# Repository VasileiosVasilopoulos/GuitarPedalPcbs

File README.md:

## Guitar Pedal Pcb Projects

Collection of Guitar and Bass Pedal pcbs 
designed with the free version of [Eagle](https://www.autodesk.com/products/eagle/free-download?plc=F360&term=1-YEAR&support=ADVANCED&quantity=1).

### Licence

The designs are free to use non-commercially.

I would not recommend using commercially since 
copyrights may apply to the schematics / fonts etc.

### List of effects

#### Fuzz 
- [Randy's Gut](Randys_Gut) (EQD Dirt Transmitter clone)
- [Zeus](Zeus) (Similar to EQD Blach Ash)

#### Octaver
- [Poseidon](Poseidon) (EQD Tentacle clone)

#### Digital
- [Deep Space](DeepSpace) (Add-on shield for teensy with Audioshield)

#### Other
- [3PDT](3PDT_Breakout) Foot Switch Breakout Board

### Resources 

I'd like to thank all the people offering to the DIY community and link some resources that helped me get familiar with designing pcb's.

Jeremy Blum's [youtube channel](https://www.youtube.com/user/sciguy14) has some good tutorials for EAGLE basics.

Effect's Layout [blog](http://effectslayouts.blogspot.com/) / [youtube](https://www.youtube.com/channel/UCuCJhqsyaGveg0PjLbAGcdQ) has a big variety of pedal designs for perfboards / pcb etching. Also a nice tutorial series for EAGLE and a pack of EAGLE libraries with focus to pcb design for pedals. 

[MadBeanPedals](https://www.madbeanpedals.com/) has some designs and tutorials for homemade pcb etching. He also has a very helpful EAGLE library.

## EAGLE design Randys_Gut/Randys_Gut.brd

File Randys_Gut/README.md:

## Randy's Gut

Fuzz

#### Status:
```diff
+ Verified
```

Schematic based on EQD Dirt Transmitter

### Board Preview: 

Front             |  Back
:-------------------------:|:-------------------------:
  |  
  |  

### Drill Template 

[Drill Template](Photos/Randys_Gut_Drill.pdf)

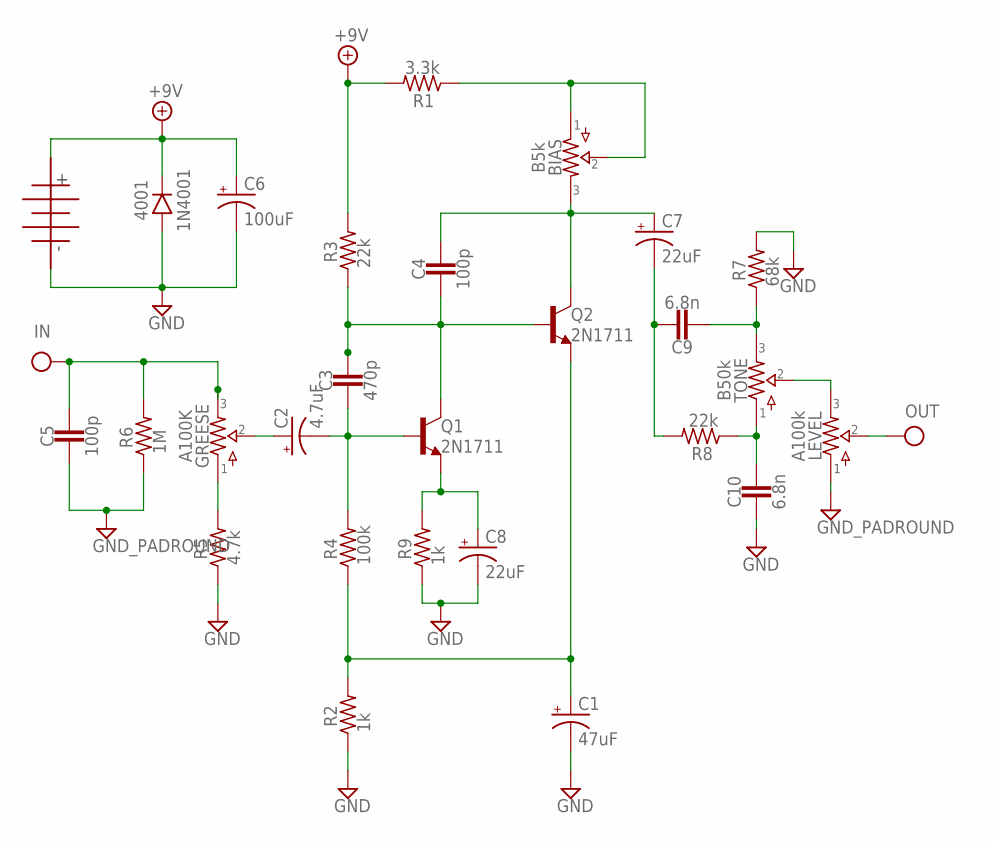
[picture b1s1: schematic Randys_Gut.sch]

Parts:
4001: 1N4001; DO41-3
BIAS: B5k; 16MM_B.MOUNT
C1: 47uF; 063_025
C2: 4.7uF; 050_020_1
C3: 470p; 0.2".SML
C4, C5: 100p; 0.2".SML
C6: 100uF; 063_025
C7, C8: 22uF; 050_020_1
C9, C10: 6.8n; 0.2".SML
GI: GND_PADROUND; ROUND
GO: GND_PADROUND; ROUND
GREESE: A100K; 16MM_B.MOUNT
IN: IN; SQUARE
LEVEL: A100k; 16MM_B.MOUNT
OUT: OUT; SQUARE
PWR: BATTERYBAT2; BATTERY2
Q1, Q2: 2N1711; TO18
R1: 3.3k; R0207/3
R2, R9: 1k; R0207/3
R3, R8: 22k; R0207/3
R4: 100k; R0207/3
R5: 4.7k; R0207/3
R6: 1M; R0207/3
R7: 68k; R0207/3
TONE: B50k; 16MM_B.MOUNT

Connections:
+9V: 4001.C, C6.+, PWR.P$1, R1.2, R3.2
C3: C2.-, C3.2, Q1.2 (B), R4.2
GND: 4001.A, C1.-, C5.2, C6.-, C8.-, C10.2, GI.1, GO.1, LEVEL.1, PWR.P$2, R2.1, R5.1, R6.1, R7.2, R9.1
IN: C5.1, GREESE.3, IN.1, R6.2
unnamed: GREESE.1, R5.2
unnamed: C2.+, GREESE.2
unnamed: C1.+, Q2.1 (E), R2.2, R4.1
unnamed: C3.1, C4.2, Q1.3 (C), Q2.2 (B), R3.1
unnamed: C8.+, Q1.1 (E), R9.2
unnamed: BIAS.3, C4.1, C7.+, Q2.3 (C)
unnamed: C7.-, C9.1, R8.2
unnamed: BIAS.1, BIAS.2, R1.1
unnamed: C9.2, R7.1, TONE.3
unnamed: C10.1, R8.1, TONE.1
unnamed: LEVEL.3, TONE.2
OUT: LEVEL.2, OUT.1

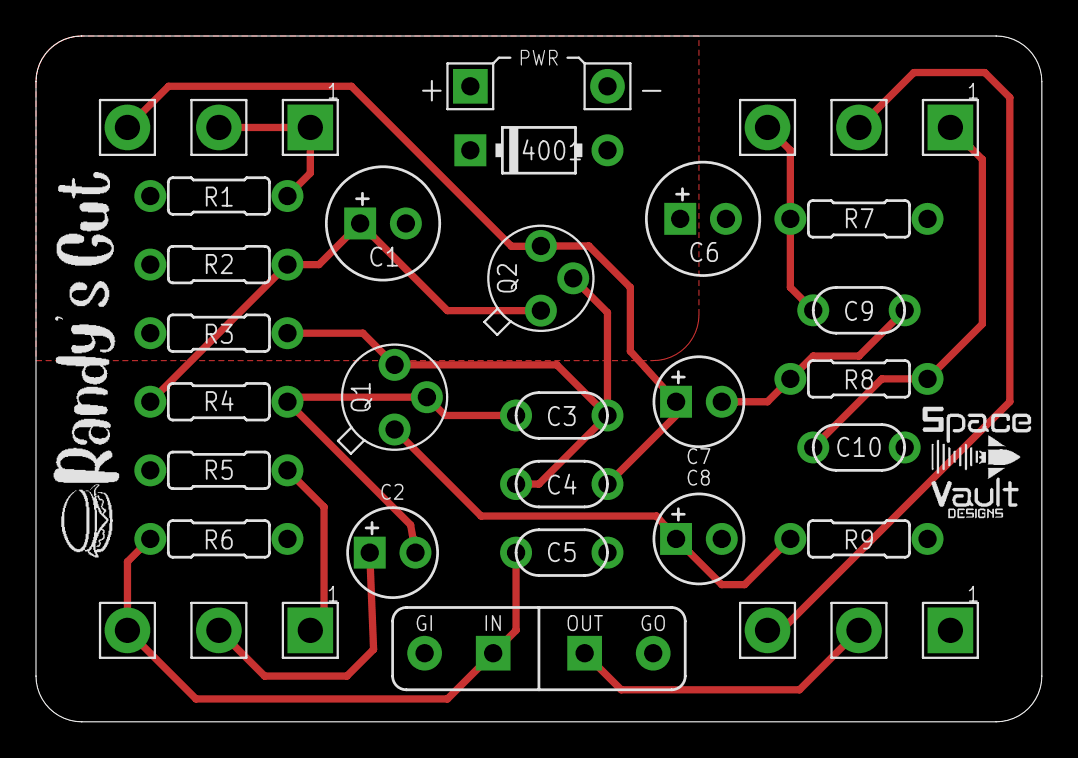
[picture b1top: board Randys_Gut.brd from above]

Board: 2 copper layers, 55.9 x 38.1 mm, 31 parts (0 on the bottom side), 16 nets.

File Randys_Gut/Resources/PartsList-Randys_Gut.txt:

_______________________________
R

1k   2
3.3k
4.7k
22k  2
68k
100k
1m
_______________________________
C 

100p  2 
470p
6.8n 2

4.7uF
22uF  2
47uF
100uF

_______________________________
D

1N4001

_______________________________
IC
2N1711 2

_______________________________
POTS

5kB
50kB
100kA 2

_______________________________
Other

2 Mono Jacks Enclosed
LED
Power Supply Socket
Pot Dusters
Pot Knobs

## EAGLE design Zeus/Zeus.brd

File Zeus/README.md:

## Zeus

Fuzz

#### Status:
```diff
+ Verified
```

Schematic similar to the EQD Dirt Transmitter.

### Board Preview: 

Front             |  Back
:-------------------------:|:-------------------------:
  |  
  |  

### Drill Template 

[Drill Template](Photos/ZeusDrill.pdf)

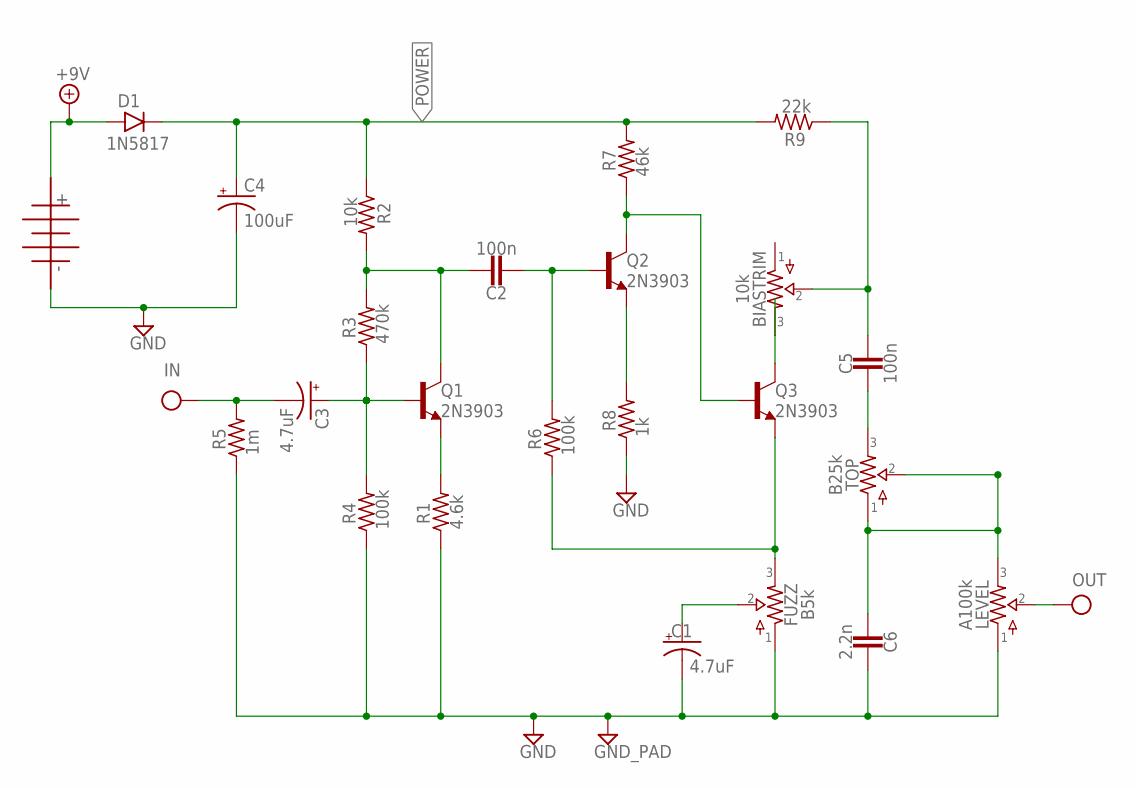
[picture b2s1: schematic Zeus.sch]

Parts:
9V: BATTERYBAT2; BATTERY2
BIASTRIM: 10k; TRIM1
C1, C3: 4.7uF; 050_020_1
C2, C5: 100n; 0.2".SML
C4: 100uF; 063_025
C6: 2.2n; 0.2".SML
D1: 1N5817; DO41-3
FUZZ: B5k; 16MM_B.MOUNT
GND: GND_PAD; SQUARE
IN: IN; SQUARE
LEVEL: A100k; 16MM_B.MOUNT
OUT: OUT; SQUARE
Q1, Q2, Q3: 2N3903; TO92
R1: 4.6k; R0207/3
R2: 10k; R0207/3
R3: 470k; R0207/3
R4, R6: 100k; R0207/3
R5: 1m; R0207/3
R7: 46k; R0207/3
R8: 1k; R0207/3
R9: 22k; R0207/3
TOP: B25k; 16MM_B.MOUNT

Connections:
+9V: 9V.P$1, D1.A
GND: 9V.P$2, C1.-, C4.-, C6.1, FUZZ.1, GND.1, LEVEL.1, R1.1, R4.1, R5.1, R8.1
IN: C3.-, IN.1, R5.2
unnamed: C2.1, Q1.1 (C), R2.2, R3.2
unnamed: C2.2, Q2.2 (B), R6.2
unnamed: C3.+, Q1.2 (B), R3.1, R4.2
unnamed: C5.2, TOP.3
unnamed: Q1.3 (E), R1.2
unnamed: Q2.3 (E), R8.2
unnamed: FUZZ.3, Q3.3 (E), R6.1
unnamed: C1.+, FUZZ.2
unnamed: BIASTRIM.3, Q3.1 (C)
unnamed: Q2.1 (C), Q3.2 (B), R7.1
unnamed: BIASTRIM.2, C5.1, R9.1
unnamed: C6.2, LEVEL.3, TOP.1, TOP.2
OUT: LEVEL.2, OUT.1
POWER: C4.+, D1.C, R2.1, R7.2, R9.2

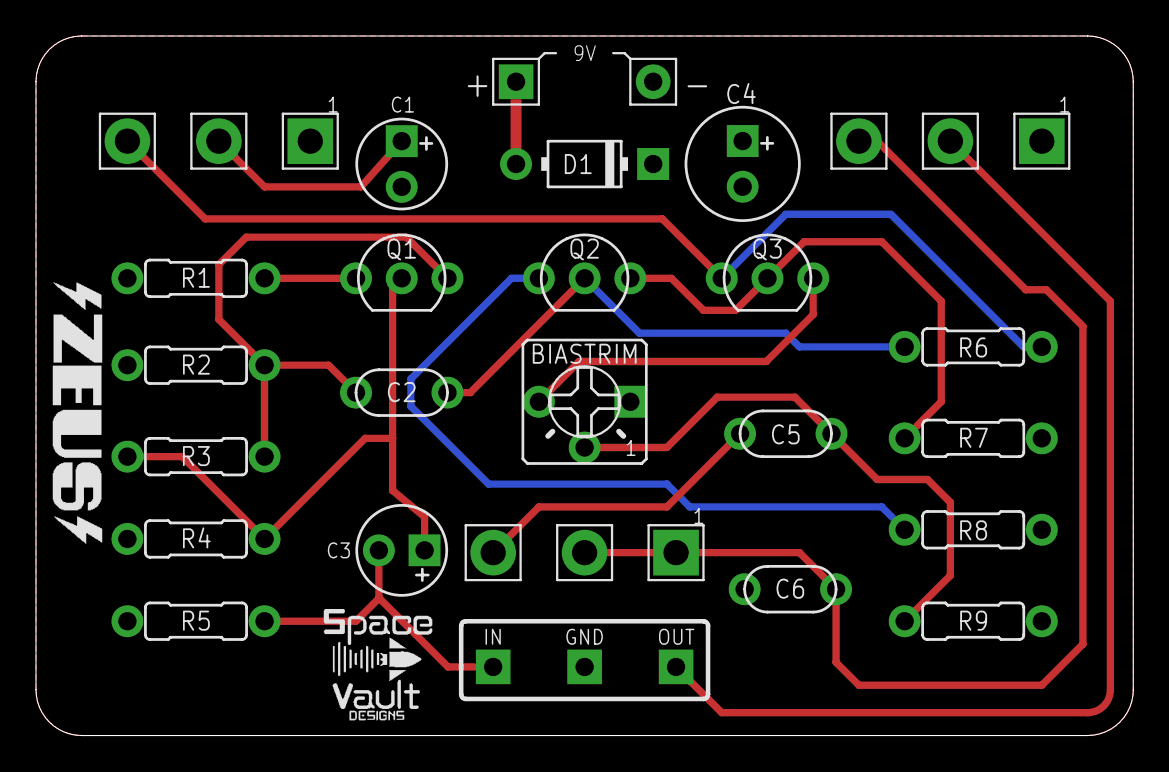
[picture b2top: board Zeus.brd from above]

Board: 2 copper layers, 61.0 x 38.9 mm, 27 parts (0 on the bottom side), 17 nets.

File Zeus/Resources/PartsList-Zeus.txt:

_______________________________
R

1k
4.6k
10k
22k
46k
100k  2
470k
1m

_______________________________
C 
2.2n
100n 2

4.7uF 2
100uF

_______________________________
D

1N5817

_______________________________
IC
2N3903  3

_______________________________
POTS
10kB Trim Small
5 kB
25kB
100kA

_______________________________
Other

2 Mono Jacks Enclosed
LED
Power Supply Socket
Pot Dusters
Pot Knobs

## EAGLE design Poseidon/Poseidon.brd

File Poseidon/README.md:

## Poseidon  	
#### Status:
```diff
+ Verified
```
Octaver  
Schematic based on the EQD Tentacle.  
### Board Preview: 

Front             |  Back
:-------------------------:|:-------------------------:
  |  
  |  

### Built pedal

Front             |  Inside
:-------------------------:|:-------------------------:
  |  

### Drill Template 

[Drill Template](Photos/PoseidonDrill.pdf)

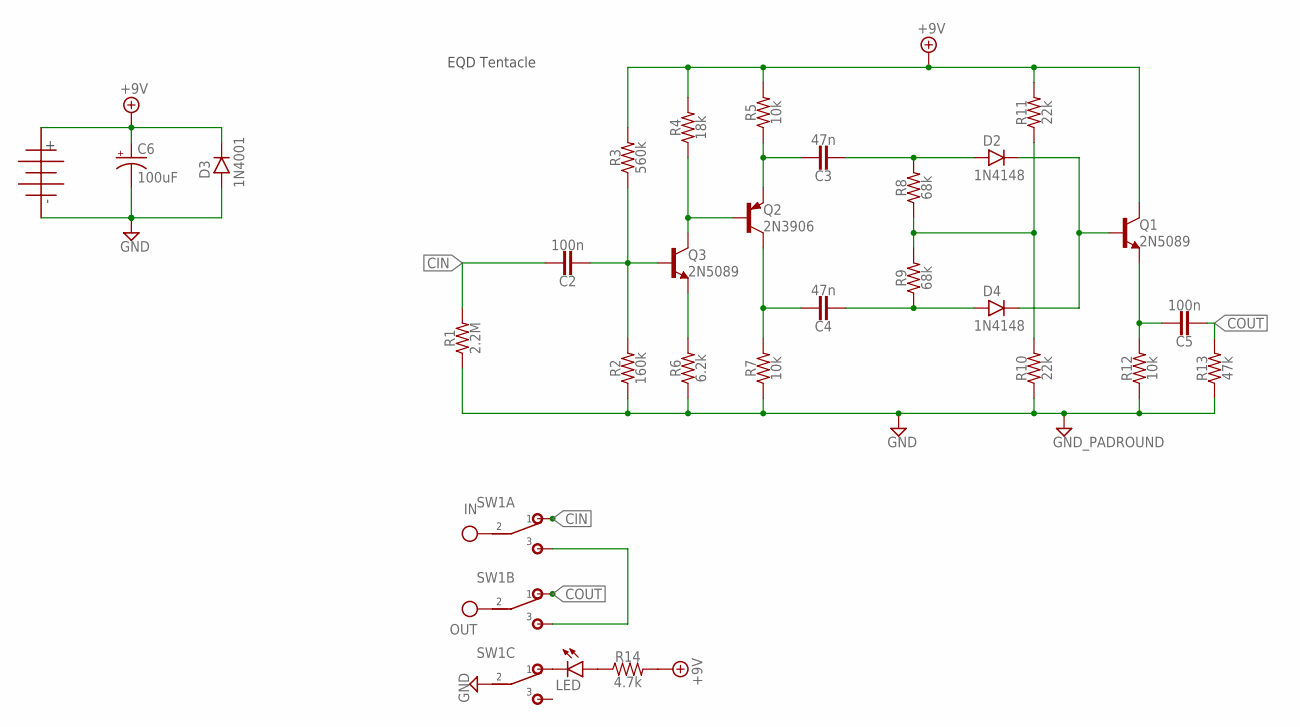
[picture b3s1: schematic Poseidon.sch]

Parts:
C2, C5: 100n; 0.2".SML
C3, C4: 47n; 0.2".SML
C6: 100uF; 063_025
D2, D4: 1N4148; DO35-3
D3: 1N4001; DO41-3
DC: BATTERYBAT2; BATTERY2
GND: GND_PADROUND; ROUND
IN: IN; SQUARE
LED: LED3MM
OUT: OUT; SQUARE
Q1, Q3: 2N5089; TO92
Q2: 2N3906; TO92
R1: 2.2M; 0.3".B
R2: 160k; 0.3".B
R3: 560k; 0.3".B
R4: 18k; 0.3".B
R5, R7, R12: 10k; 0.3".B
R6: 6.2k; 0.3".B
R8, R9: 68k; 0.3".B
R10, R11: 22k; 0.3".B
R13: 47k; 0.3".B
R14: 4.7k; 0.3".B
SW1: 3PDT

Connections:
+9V: C6.+, D3.C, DC.P$1, Q1.1 (C), R3.2, R4.2, R5.2, R11.2, R14.2
CIN: C2.1, R1.2, SW1.A1 (1)
COUT: C5.2, R13.2, SW1.B1 (1)
GND: C6.-, D3.A, DC.P$2, GND.1, R1.1, R2.1, R6.1, R7.1, R10.1, R12.1, R13.1, SW1.C2 (2)
IN: IN.1, SW1.A2 (2)
unnamed: SW1.A3 (3), SW1.B3 (3)
unnamed: C2.2, Q3.2 (B), R2.2, R3.1
unnamed: LED.K (C), SW1.C1 (1)
unnamed: Q3.3 (E), R6.2
unnamed: LED.A, R14.1
unnamed: Q2.2 (B), Q3.1 (C), R4.1
unnamed: C3.1, Q2.3 (E), R5.1
unnamed: C4.1, Q2.1 (C), R7.2
unnamed: C4.2, D4.A, R9.1
unnamed: R8.1, R9.2, R10.2, R11.1
unnamed: C3.2, D2.A, R8.2
unnamed: D2.C, D4.C, Q1.2 (B)
unnamed: C5.1, Q1.3 (E), R12.2
OUT: OUT.1, SW1.B2 (2)

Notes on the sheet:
EQD Tentacle

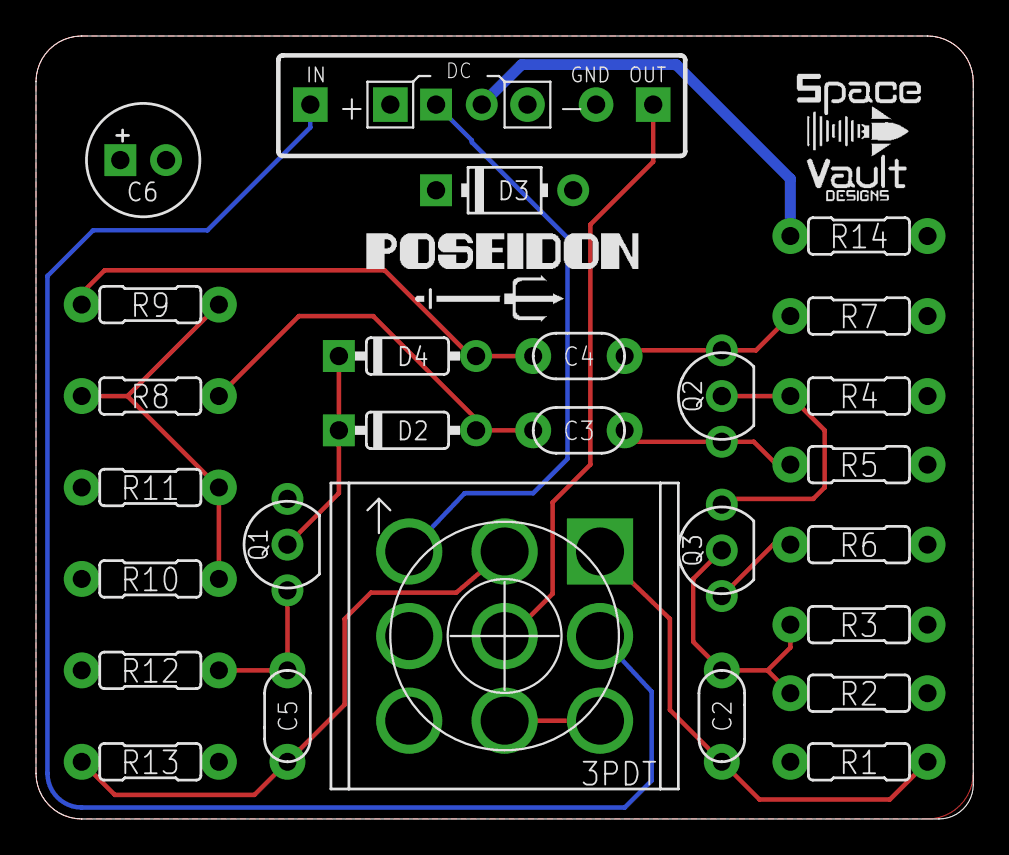
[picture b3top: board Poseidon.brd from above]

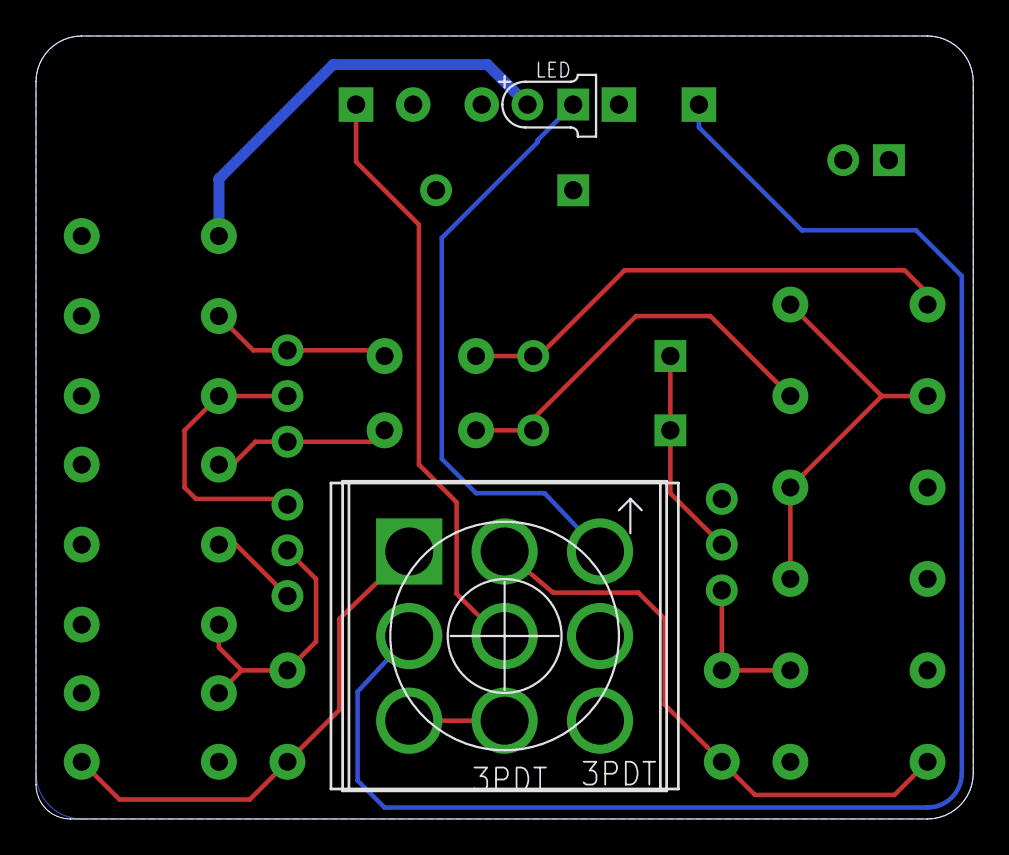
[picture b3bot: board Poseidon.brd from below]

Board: 2 copper layers, 52.1 x 43.5 mm, 32 parts (2 on the bottom side), 19 nets.

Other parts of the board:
U$1: 3PDT

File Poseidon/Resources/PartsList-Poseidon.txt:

_______________________________
R

6.2k
10k  3
18k
22k  2
47k
68k  2
160k
560k
2.2m
_______________________________
C 

47n 2
100n 2

100uF

_______________________________
D
1N4001
1N4148 2

_______________________________
IC
2N3906
2N5089 2

_______________________________
Other

2 Mono Jacks Enclosed
LED
Power Supply Socket

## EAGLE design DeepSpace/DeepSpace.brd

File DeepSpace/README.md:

## Deep Space

### Add-on shield used with [Teensy 4.0](https://www.pjrc.com/store/teensy40.html) and the [Teensy Audioshield](https://www.pjrc.com/store/teensy3_audio.html)

#### Status:
```diff
+ Verified except the Phantom power switch
```

Circuit to add guitar and microphone input to the teensy 4.0 audio shield and output the signal to an amplifier 

The board is designed to fit in a 1590BB Enclosure.

### Features:

- Guitar input buffer using a TL072.
- Mircophone input buffer + preamplifier using the SSM2019 chip.
- Teensy output buffer
- 3 Potentiometer connected to the teensy (configured through the software).

### Board Preview: 

Front             |  Back
:-------------------------:|:-------------------------:
  |  
  |  
  |  
  |  

### Drill Template 

[Drill Template](Photos/DeepSpace_Drill.pdf)

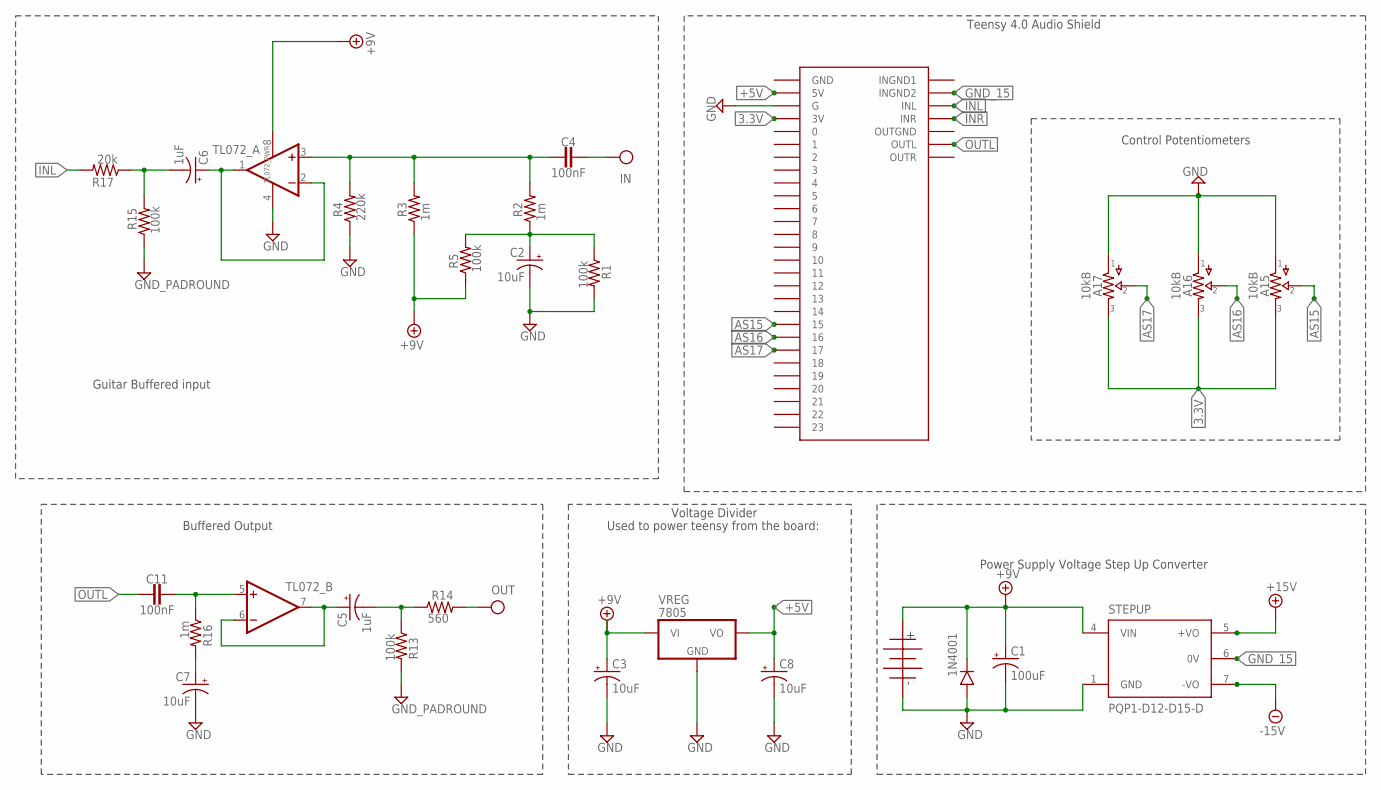
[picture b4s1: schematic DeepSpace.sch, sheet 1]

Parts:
1N4001: DO41.3; DO41-3
A15, A16, A17: 10kB; 16MM_B.MOUNT
AS1: teensy audio shield; AUDIOSHIELD; MPN 4384
C1: 100uF; 063_025
C2, C3, C7, C8: 10uF; 050_020_1
C4, C11: 100nF; 0.2".SML
C5, C6: 1uF; 050_020_1
GI: GND_PADROUND; ROUND
GO: GND_PADROUND; ROUND
OUT: OUT; SQUARE
PWR: BATTERYBAT2; BATTERY2
R1, R5, R13, R15: 100k; R0207/3
R2, R3, R16: 1m; R0207/3
R4: 220k; R0207/3
R14: 560; R0207/3
R17: 20k; R0207/3
STEPUP: PQP1-D12-D15-D; CONV_PQP1-D12-D15-D
TL072: DUALTH; DIL08
VREG: 7805; TO92-
ΙΝ: IN; SQUARE

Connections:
3.3V: A15.3, A16.3, A17.3, AS1.3V
10UF: C2.+, R1.1, R2.1, R5.2
+5V: AS1.5V, C8.+, VREG.3 (VO)
+9V: 1N4001.C, C1.+, C3.+, PWR.P$1, R3.1, R5.1, STEPUP.4 (VIN), TL072.8 (V+), VREG.1 (VI)
+15V: STEPUP.5 (+VO); also elsewhere on the board
-VC: STEPUP.7 (-VO); also elsewhere on the board
AS15: A15.2, AS1.15
AS16: A16.2, AS1.16
AS17: A17.2, AS1.17
GND: 1N4001.A, A15.1, A16.1, A17.1, AS1.G, C1.-, C2.-, C3.-, C7.-, C8.-, GI.1, GO.1, PWR.P$2, R1.2, R4.1, R13.2, R15.1, STEPUP.1 (GND), TL072.4 (V-), VREG.2 (GND)
GND_15: AS1.INGND2, STEPUP.6 (0V); also elsewhere on the board
IN: C4.1, ΙΝ.1
INL: AS1.INL, R17.2
INR: AS1.INR; also elsewhere on the board
unnamed: C7.+, R16.2
unnamed: C6.+, TL072.1 (OUT), TL072.2 (-IN)
unnamed: C6.-, R15.2, R17.1
unnamed: C4.2, R2.2, R3.2, R4.2, TL072.3 (+IN)
unnamed: C11.1, R16.1, TL072.5 (+IN)
unnamed: C5.+, TL072.6 (-IN), TL072.7 (OUT)
unnamed: C5.-, R13.1, R14.1
OUT: OUT.1, R14.2
OUTL: AS1.OUTL, C11.2

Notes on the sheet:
Power Supply Voltage Step Up Converter
Teensy 4.0 Audio Shield
Control Potentiometers
Used to power teensy from the board:
Voltage Divider
Guitar Buffered input
Buffered Output

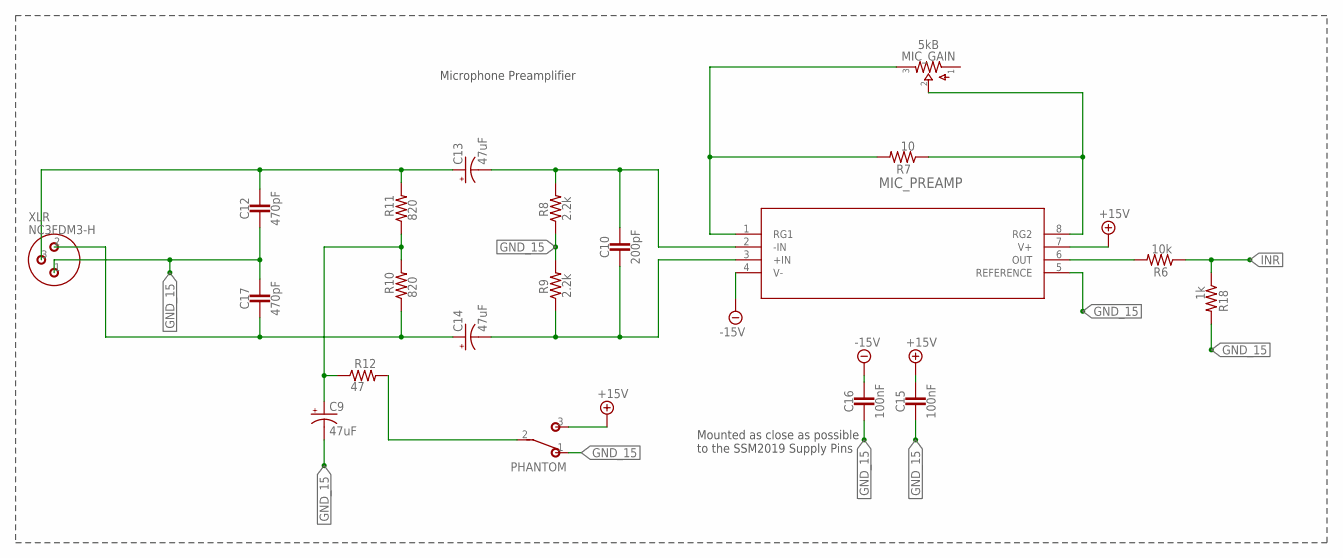
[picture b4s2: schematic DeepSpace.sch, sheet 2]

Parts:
C9: 47uF; 050_020_1
C10: 200pF; 0.2".SML
C12, C17: 470pF; 0.2".SML
C13, C14: 47uF; 063_025
C15, C16: 100nF; 0.2".SML
MIC_GAIN: 5kB; TRIM1
MIC_PREAMP: SSM2019BNZ; N_8_ADI; MPN SSM2019BRNZ
PHANTOM: SPDTPADS; SPDT
R6: 10k; R0207/3
R7: 10; R0207/3
R8, R9: 2.2k; R0207/3
R10, R11: 820; R0207/3
R12: 47; R0207/3
R18: 1k; R0207/3
XLR: NC3FDM3-H; XLR_PADS

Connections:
+15V: C15.1, MIC_PREAMP.7 (V+), PHANTOM.3 (S); also elsewhere on the board
-VC: C16.1, MIC_PREAMP.4 (V-); also elsewhere on the board
GND_15: C9.-, C12.2, C15.2, C16.2, C17.1, MIC_PREAMP.5 (REFERENCE), PHANTOM.1 (O), R8.1, R9.2, R18.2, XLR.1; also elsewhere on the board
INR: R6.1, R18.1; also elsewhere on the board
unnamed: MIC_GAIN.3, MIC_PREAMP.1 (RG1), R7.2
unnamed: MIC_GAIN.2, MIC_PREAMP.8 (RG2), R7.1
unnamed: C10.1, C13.-, MIC_PREAMP.2 (-IN), R8.2
unnamed: C10.2, C14.-, MIC_PREAMP.3 (+IN), R9.1
unnamed: C9.+, R10.2, R11.1, R12.1
unnamed: PHANTOM.2, R12.2
unnamed: MIC_PREAMP.6 (OUT), R6.2
XLR2: C12.1, C13.+, R11.2, XLR.3
XLR2-SSM3: C14.+, C17.2, R10.1, XLR.2

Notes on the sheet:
Mounted as close as possible to the SSM2019 Supply Pins
Microphone Preamplifier

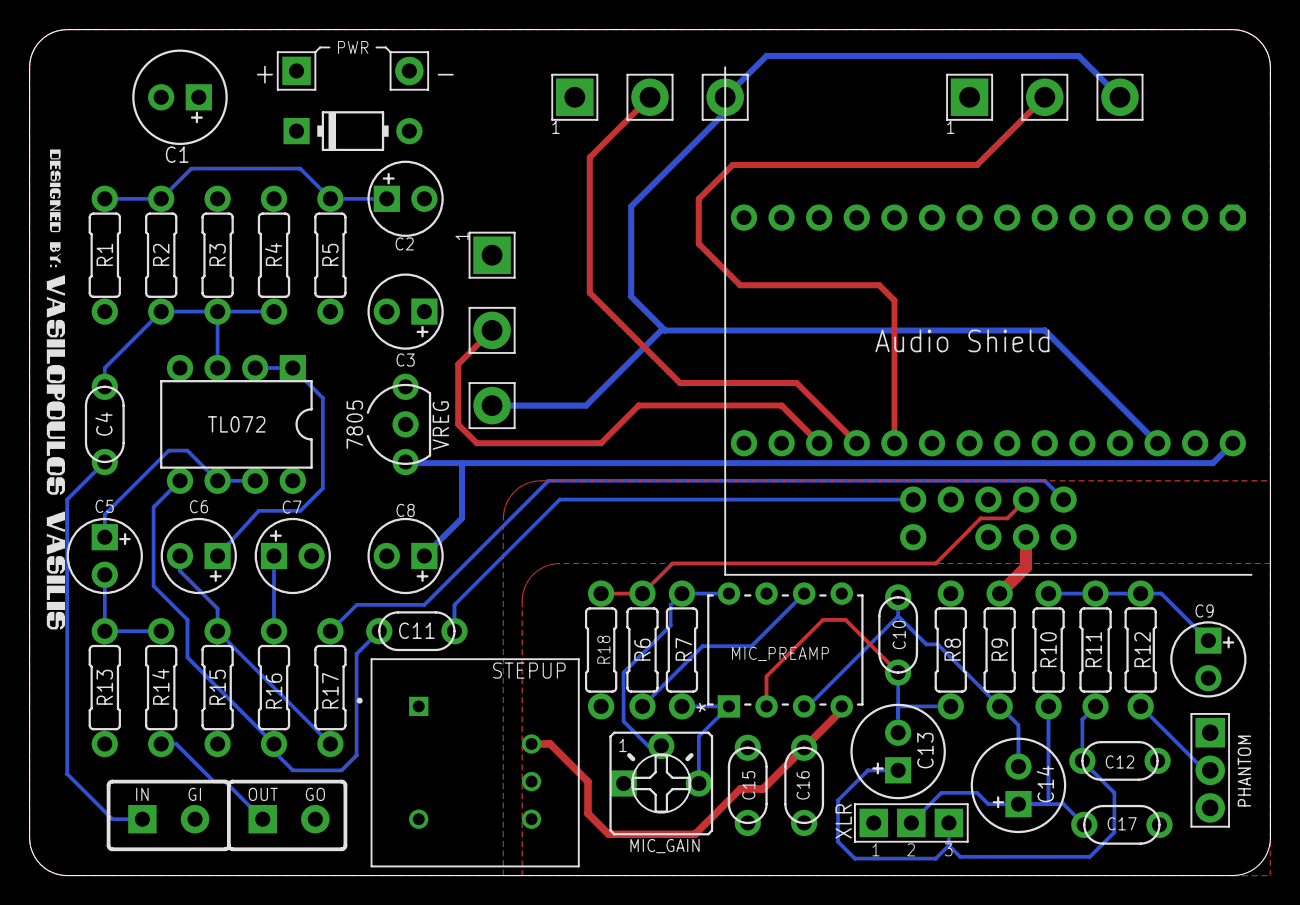
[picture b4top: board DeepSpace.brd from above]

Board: 2 copper layers, 83.8 x 57.1 mm, 52 parts (0 on the bottom side), 32 nets.

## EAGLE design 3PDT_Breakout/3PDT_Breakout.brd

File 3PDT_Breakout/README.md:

## 3PDT Breakout Board

3PDT Breakout board with current limiting resistor and 2 spots for 3mm or 5mm LED (right or left of the switch).

#### Status:
```diff
+ Verified
```

3PDT Switches have small variations in dimensions so make sure to check your switch documentation and modify the footprint if needed.

### Board Preview: 

Front             |  Back
:-------------------------:|:-------------------------:
  |  
  |

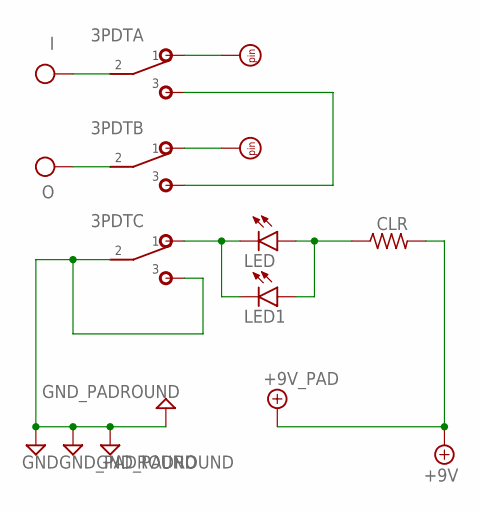
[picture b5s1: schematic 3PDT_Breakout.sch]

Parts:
3PDT: 3PDT
CI: PADS.SQR_NL; PAD4
CLR: RESISTORS.3B; R0207/3
CO: PADS.SQR_NL; PAD4
GI: GND_PADROUND; ROUND
GND: GND_PADROUND; ROUND
GO: GND_PADROUND; ROUND
I: IN; SQUARE
LED, LED1: LED3MM
O: OUT; SQUARE
V+: +9V_PAD; SQUARE

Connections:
+9V: CLR.2, V+.1
GND: 3PDT.C2 (2), 3PDT.C3 (3), GI.1, GND.1, GO.1
IN: 3PDT.A2 (2), I.1
unnamed: 3PDT.C1 (1), LED.K (C), LED1.K (C)
unnamed: CLR.1, LED.A, LED1.A
unnamed: 3PDT.B1 (1), CO.P$1
unnamed: 3PDT.A1 (1), CI.P$1
unnamed: 3PDT.A3 (3), 3PDT.B3 (3)
OUT: 3PDT.B2 (2), O.1

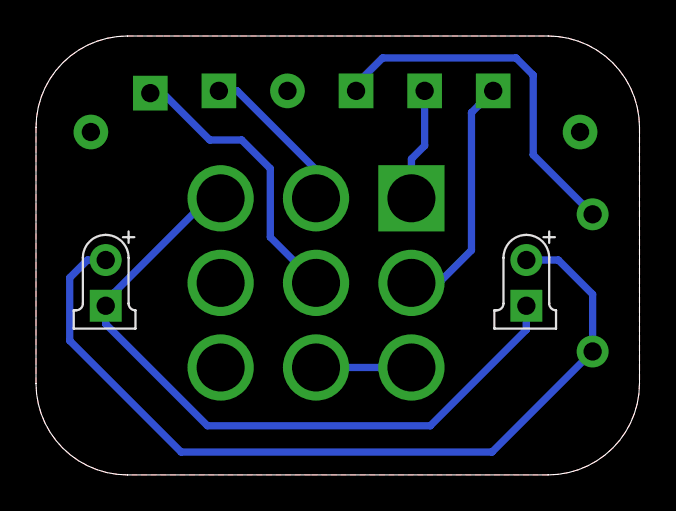
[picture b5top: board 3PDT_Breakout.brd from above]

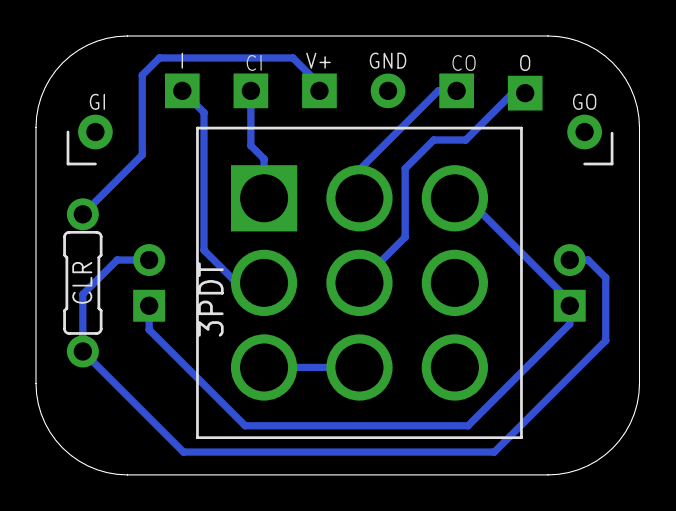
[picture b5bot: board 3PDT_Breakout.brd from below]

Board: 2 copper layers, 33.5 x 24.4 mm, 12 parts (8 on the bottom side), 9 nets.

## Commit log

2020-11-23 Added Randy's Gut
2020-11-23 Adding effects
2020-11-23 Added DeepSpace
2020-11-23 Added Zeus
2020-11-23 Added Poseidon
2020-11-23 Added 3PDT
2020-11-23 Added Deep Space
2020-11-23 Added README
2020-11-23 Changes to README
2020-11-24 Added preview images
2020-12-01 Minor Changes
2020-12-31 Adding photos
2020-12-31 Change to readme
2021-01-25 Verified Deep Space, Zeus
2021-01-25 Added logo
2021-02-07 README changes
2021-05-27 Added gitignore

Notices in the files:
parts and their libraries:
SparkFun-Aesthetics: Licensing: Creative Commons ShareAlike 4.0 International - https://creativecommons.org/licenses/by-sa/4.0
